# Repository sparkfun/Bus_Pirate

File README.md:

Bus Pirate
==========

*Bus Pirate [(TOL-12942)](https://www.sparkfun.com/products/12942)*

This is a troubleshooting tool that communicates between a PC and any embedded device over most standard serial protocols, which
include I<sup>2</sup>C, SPI, and asynchronous serial.

Repository Contents
-------------------

* **/Hardware** &mdash; All Eagle design files (.brd, .sch)
* **/Production** &mdash; Production panel file (.brd)
* **/Software** &mdash; Minimal Python example demonstrating binary mode

Documentation
--------------
* **[Hookup Guide](https://learn.sparkfun.com/tutorials/bus-pirate-v36a-hookup-guide)** &mdash; Basic hookup guide for the Bus Pirate.
* **[SparkFun Fritzing repo](https://github.com/sparkfun/Fritzing_Parts)** &mdash; Fritzing diagrams for SparkFun products.

Product Versions
----------------
* [TOL-12942](https://www.sparkfun.com/products/12942) &mdash; Serial protocol troubleshooting tool

Version History
---------------
* [v3.6a](https://www.sparkfun.com/products/12942) &mdash; Updated main connector wire colors/locations and improved power regulation
* [v36](https://www.sparkfun.com/products/retired/9544) &mdash; Original version produced by SparkFun

License Information
-------------------

This product is _**open source**_!

Please review the LICENSE.md file for license information.

If you have any questions or concerns on licensing, please contact techsupport@sparkfun.com.

Distributed as-is; no warranty is given.

- Your friends at SparkFun.

This is a collaboration with Ian Lesnet.

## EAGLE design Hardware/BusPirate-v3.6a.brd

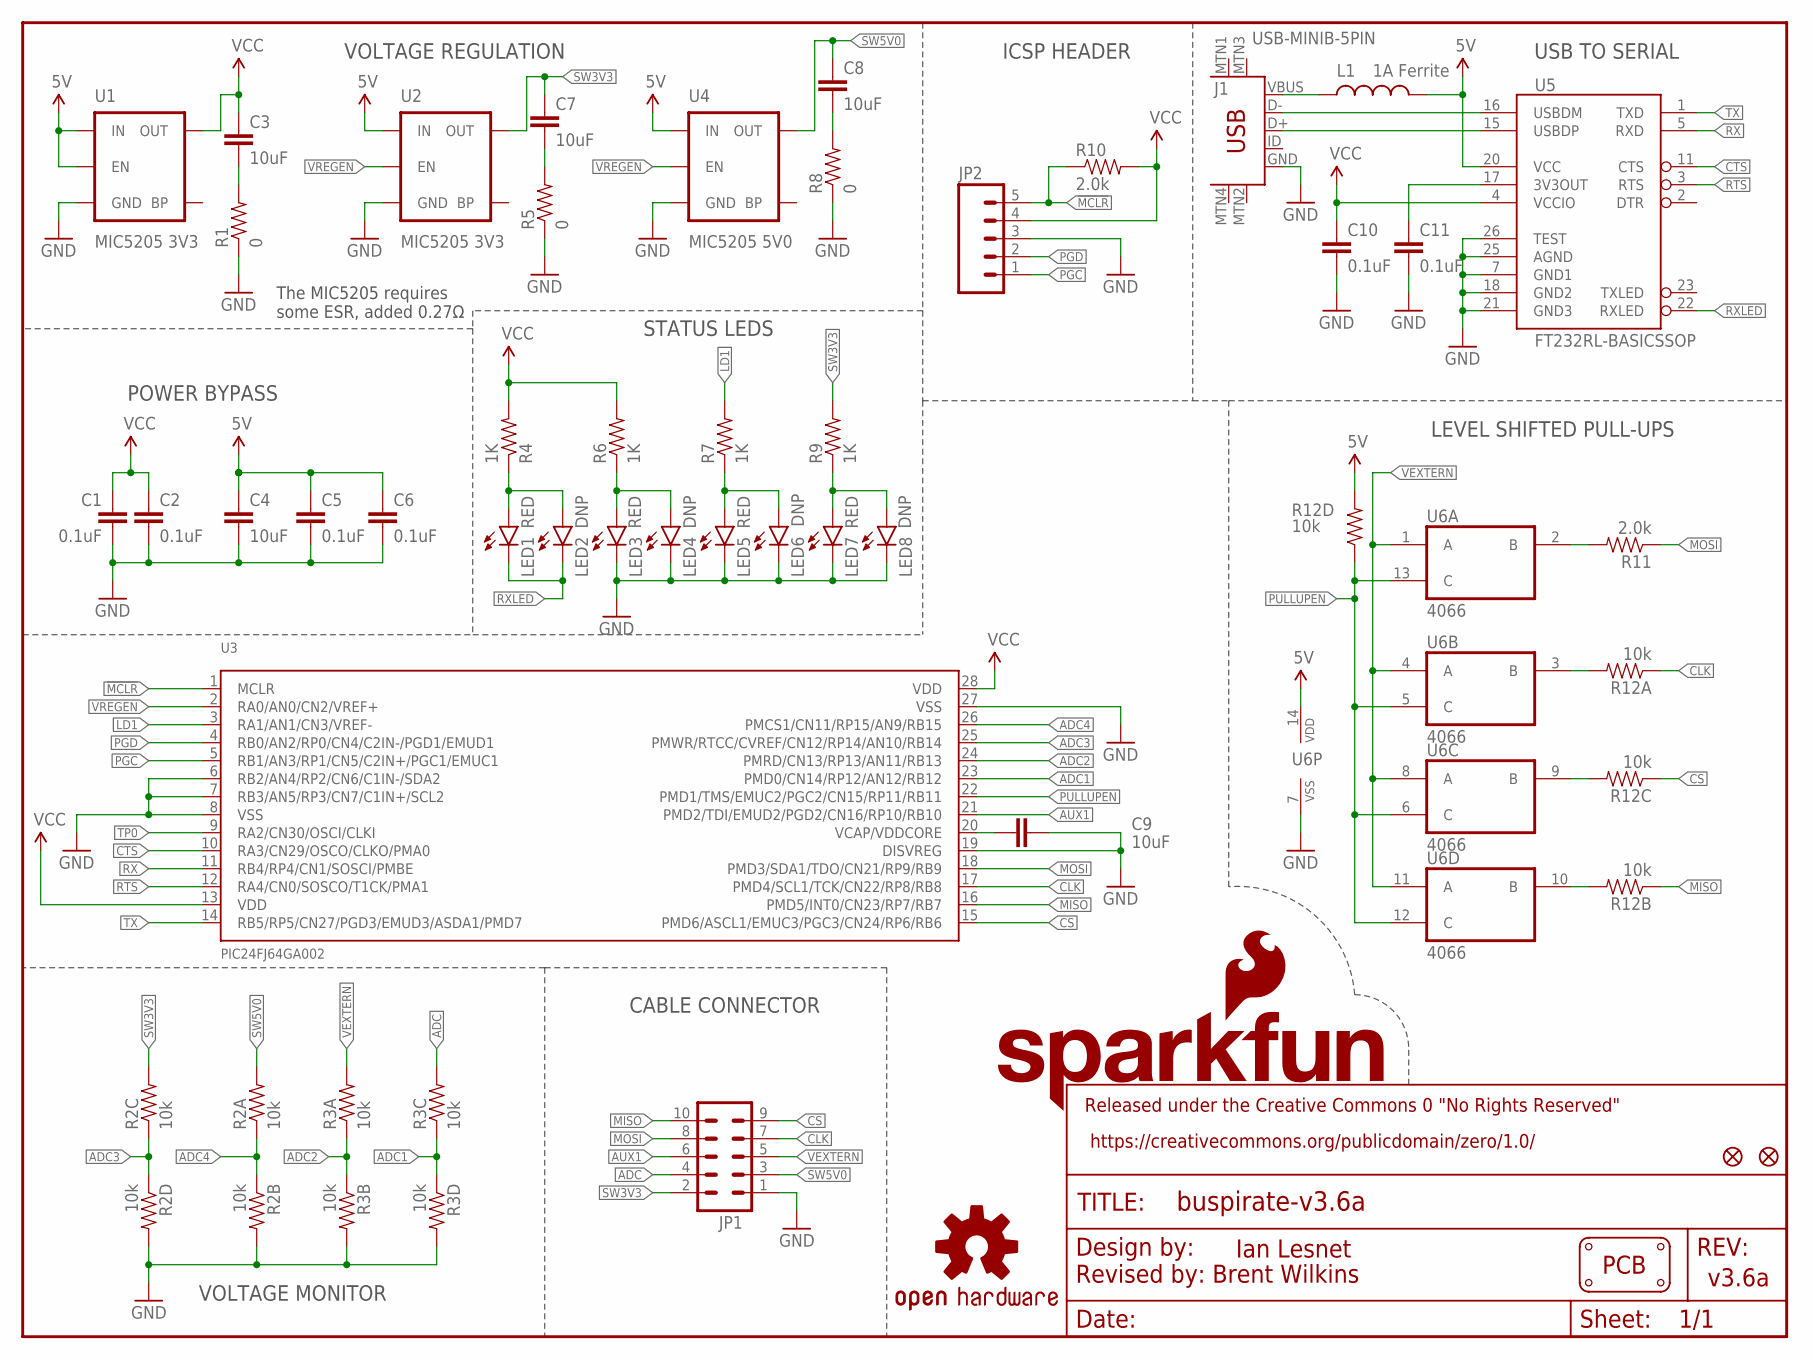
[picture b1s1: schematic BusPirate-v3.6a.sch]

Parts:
C1, C2, C5, C6, C10, C11: 0.1uF; 0603-CAP
C3, C4, C7, C8, C9: 10uF; 0805-CAP
FID1, FID2: FIDUCIAL1X2; FIDUCIAL-1X2
J1: USB-MINIB-5PIN; USB-MINIB
JP1: M05X2SHD_SMD; 2X5-SHROUDED_SMD
JP2: M05PTH; 1X05
L1: 1A Ferrite; 0603
LED1, LED3, LED5, LED7: RED; LED-0603
LED2, LED4, LED6, LED8: DNP; LED-0603
LOGO1: OSHW-LOGOL; OSHW-LOGO-L
LOGO2: SFE_LOGO_NAME_FLAME.1_INCH; SFE_LOGO_NAME_FLAME_.1
PCB1: PCB_DP_RECTANGLE-37X60; DP6037_V1
R1, R5, R8: 0; 0603
R2, R3, R12: 10k; 4XARRAY
R4, R6, R7, R9: 1K; 0603-RES
R10, R11: 2.0k; 0603-RES
U1, U2: MIC5205 3V3; SOT23-5
U3: PIC24FJ64GA002; SSOP28
U4: MIC5205 5V0; SOT23-5
U5: FT232RL-BASICSSOP; SSOP28DB
U6: 4066; TSSOP14

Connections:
5V: C4.1, C5.1, C6.1, L1.2, R12.5 (2), U1.1 (IN), U1.3 (EN), U2.1 (IN), U4.1 (IN), U5.20 (VCC), U6.14 (VDD)
!MCLR: JP2.5, R10.1, U3.1 (MCLR)
$N26: J1.VBUS, L1.1
ADC: JP1.4, R3.6 (2)
ADC1: R3.3 (1), R3.4 (1), U3.23 (PMD0/CN14/RP12/AN12/RB12)
ADC2: R3.1, R3.2 (1), U3.24 (PMRD/CN13/RP13/AN11/RB13)
ADC3: R2.3 (1), R2.4 (1), U3.25 (PMWR/RTCC/CVREF/CN12/RP14/AN10/RB14)
ADC4: R2.1, R2.2 (1), U3.26 (PMCS1/CN11/RP15/AN9/RB15)
AUX1: JP1.6, U3.21 (PMD2/TDI/EMUD2/PGD2/CN16/RP10/RB10)
CLK: JP1.7, R12.1, U3.17 (PMD4/SCL1/TCK/CN22/RP8/RB8)
CS: JP1.9, R12.3 (1), U3.15 (PMD6/ASCL1/EMUC3/PGC3/CN24/RP6/RB6)
CTS: U3.10 (RA3/CN29/OSCO/CLKO/PMA0), U5.11 (CTS)
D+: J1.D+, U5.15 (USBDP)
D-: J1.D-, U5.16 (USBDM)
GND: C1.2, C2.2, C4.2, C5.2, C6.2, C9.2, C10.2, C11.2, J1.GND, JP1.1, JP2.3, LED3.C, LED4.C, LED5.C, LED6.C, LED7.C, LED8.C, R1.1, R2.5 (2), R2.7 (2), R3.5 (2), R3.7 (2), R5.1, R8.1, U1.2 (GND), U2.2 (GND), U3.6 (RB2/AN4/RP2/CN6/C1IN-/SDA2), U3.7 (RB3/AN5/RP3/CN7/C1IN+/SCL2), U3.8 (VSS), U3.19 (DISVREG), U3.27 (VSS), U4.2 (GND), U5.7 (GND1), U5.18 (GND2), U5.21 (GND3), U5.25 (AGND), U5.26 (TEST), U6.7 (VSS)
LD1: R7.2, U3.3 (RA1/AN1/CN3/VREF-)
MISO: JP1.10, R12.2 (1), U3.16 (PMD5/INT0/CN23/RP7/RB7)
MOSI: JP1.8, R11.1, U3.18 (PMD3/SDA1/TDO/CN21/RP9/RB9)
unnamed: R11.2, U6.2 (B)
unnamed: R12.6 (2), U6.9 (B)
unnamed: C9.1, U3.20 (VCAP/VDDCORE)
unnamed: R12.7 (2), U6.10 (B)
unnamed: R12.8 (2), U6.3 (B)
unnamed: LED5.A, LED6.A, R7.1
unnamed: LED3.A, LED4.A, R6.1
unnamed: C3.2, R1.2
unnamed: C11.1, U5.17 (3V3OUT)
unnamed: C7.2, R5.2
unnamed: C8.2, R8.2
unnamed: LED1.A, LED2.A, R4.1
unnamed: LED7.A, LED8.A, R9.1
PGC: JP2.1, U3.5 (RB1/AN3/RP1/CN5/C2IN+/PGC1/EMUC1)
PGD: JP2.2, U3.4 (RB0/AN2/RP0/CN4/C2IN-/PGD1/EMUD1)
PULLUPEN: R12.4 (1), U3.22 (PMD1/TMS/EMUC2/PGC2/CN15/RP11/RB11), U6.5 (C), U6.6 (C), U6.12 (C), U6.13 (C)
RTS: U3.12 (RA4/CN0/SOSCO/T1CK/PMA1), U5.3 (RTS)
RX: U3.11 (RB4/RP4/CN1/SOSCI/PMBE), U5.5 (RXD)
RXLED: LED1.C, LED2.C, U5.22 (RXLED)
SW3V3: C7.1, JP1.2, R2.6 (2), R9.2, U2.5 (OUT)
SW5V0: C8.1, JP1.3, R2.8 (2), U4.5 (OUT)
TP0: U3.9 (RA2/CN30/OSCI/CLKI)
TX: U3.14 (RB5/RP5/CN27/PGD3/EMUD3/ASDA1/PMD7), U5.1 (TXD)
VCC: C1.1, C2.1, C3.1, C10.1, JP2.4, R4.2, R6.2, R10.2, U1.5 (OUT), U3.13 (VDD), U3.28 (VDD), U5.4 (VCCIO)
VEXTERN: JP1.5, R3.8 (2), U6.1 (A), U6.4 (A), U6.8 (A), U6.11 (A)
VREGEN: U2.3 (EN), U3.2 (RA0/AN0/CN2/VREF+), U4.3 (EN)

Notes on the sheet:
Revised by: Brent Wilkins
Ian Lesnet
v3.6a
VOLTAGE REGULATION
VOLTAGE MONITOR
USB TO SERIAL
STATUS LEDS
POWER BYPASS
ICSP HEADER
LEVEL SHIFTED PULL-UPS
CABLE CONNECTOR
The MIC5205 requires some ESR, added 0.27Ω
Date:
Sheet:
REV:
TITLE:
Released under the Creative Commons 0 "No Rights Reserved"
https://creativecommons.org/publicdomain/zero/1.0/
Design by:

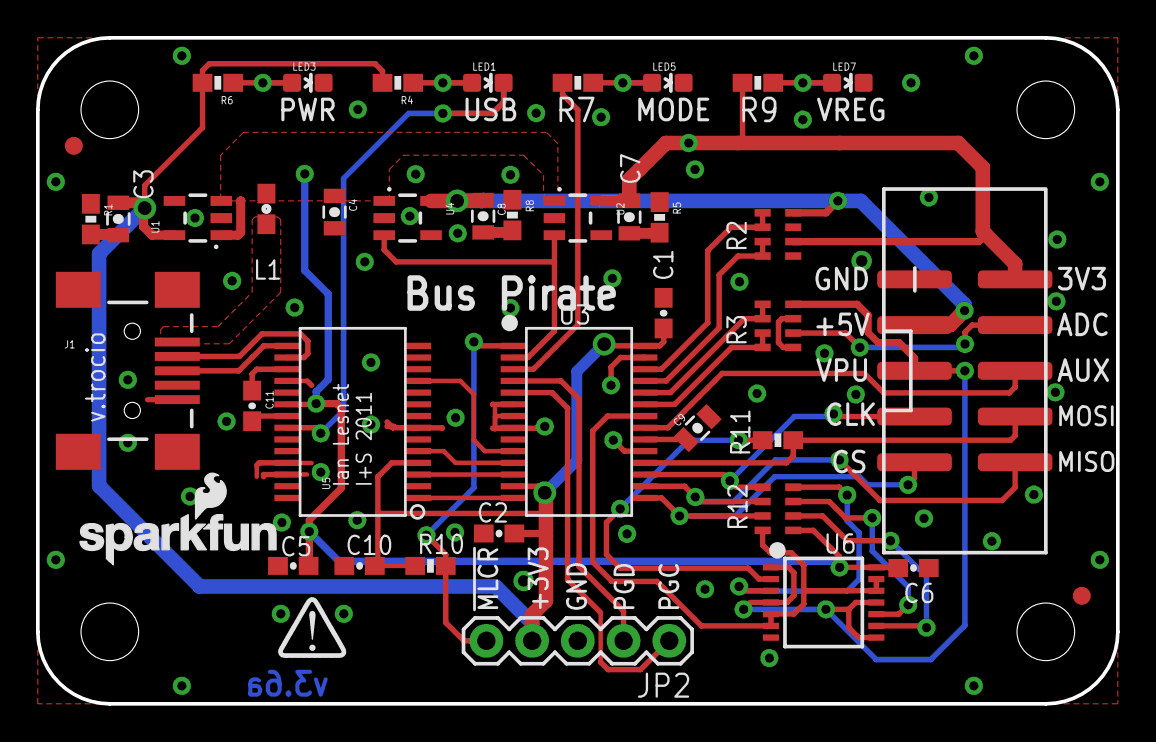
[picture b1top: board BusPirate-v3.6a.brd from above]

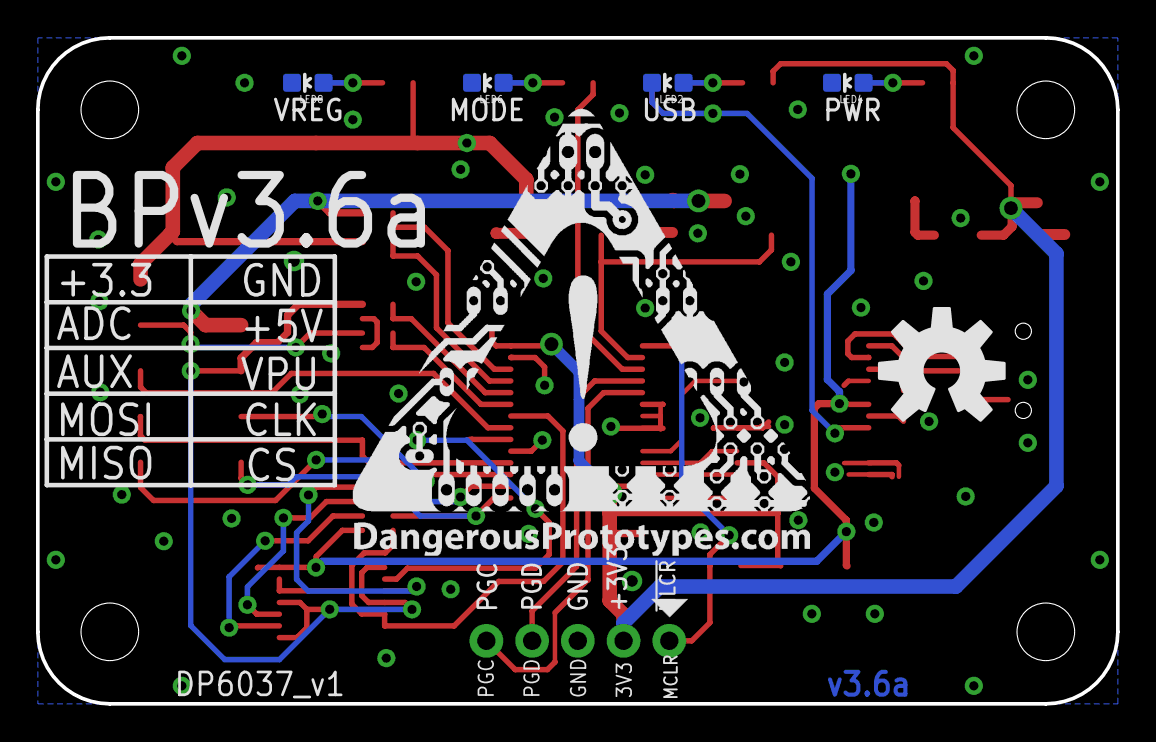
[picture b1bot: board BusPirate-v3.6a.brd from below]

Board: 2 copper layers, 60.0 x 37.0 mm, 48 parts (6 on the bottom side), 43 nets.

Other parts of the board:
U$1: DP-LOGO
U$3: DP_LOGO_ART_1X1

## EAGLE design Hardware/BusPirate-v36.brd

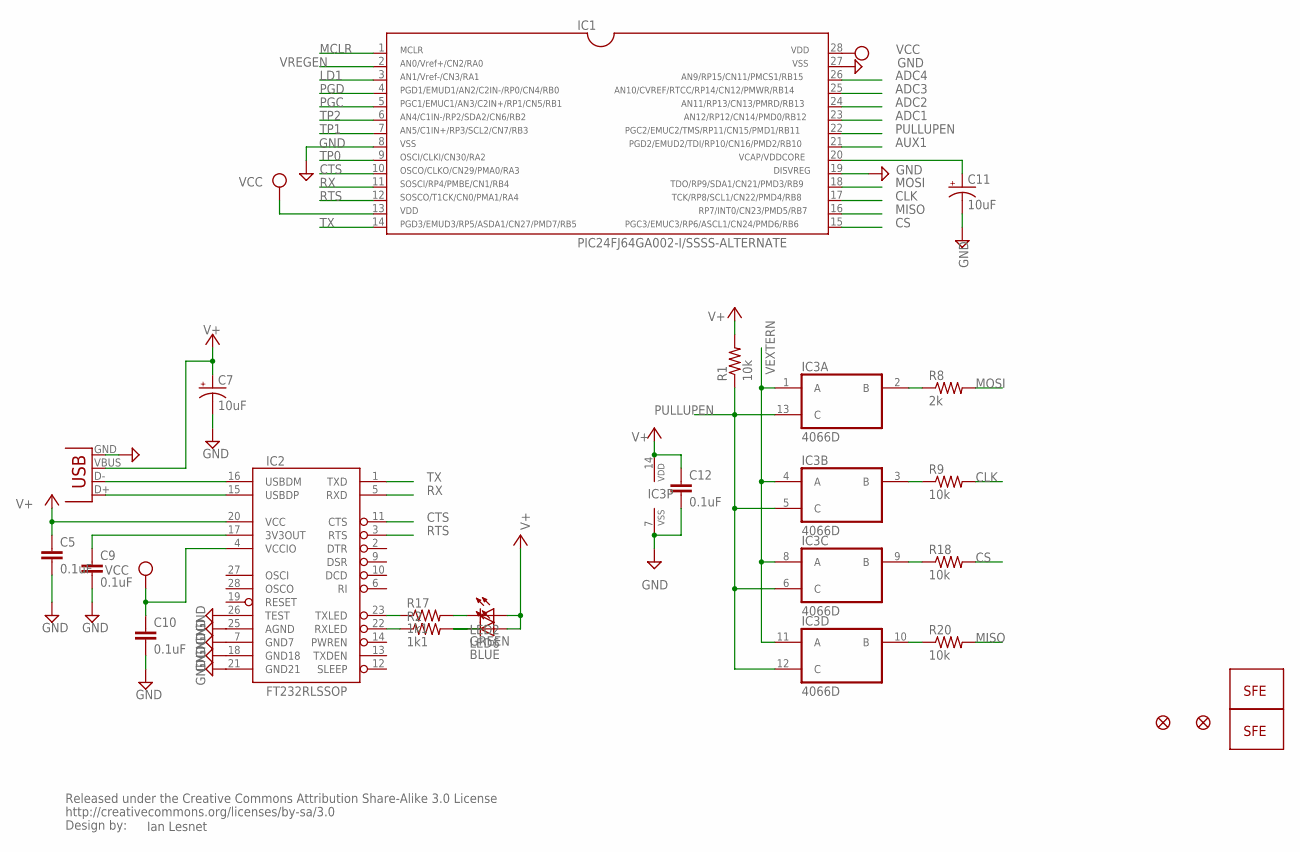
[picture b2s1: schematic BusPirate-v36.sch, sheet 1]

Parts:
C5, C9, C10, C12: 0.1uF; 0402-CAP
C7, C11: 10uF; EIA3216
IC1: PIC24FJ64GA002-I/SSSS-ALTERNATE; SSOP28DB
IC2: FT232RLSSOP; SSOP28DB
IC3: 4066D; SO14
J1: USBSMD; USB-MINIB
JP1, JP2: LOGO-SFENEW; SFE-NEW-WEBLOGO
JP3, JP4: FIDUCIAL1X2; FIDUCIAL-1X2
LED2: GREEN; LED-0603
LED6: BLUE; LED-0603
R1, R9, R18, R20: 10k; 0402-RES
R2, R17: 1k1; 0402-RES
R8: 2k; 0402-RES
U$2: CREATIVE_COMMONS

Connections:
ADC1: IC1.23; also elsewhere on the board
ADC2: IC1.24; also elsewhere on the board
ADC3: IC1.25; also elsewhere on the board
ADC4: IC1.26; also elsewhere on the board
AUX1: IC1.21; also elsewhere on the board
CLK: IC1.17, R9.2; also elsewhere on the board
CS: IC1.15, R18.2; also elsewhere on the board
CTS: IC1.10, IC2.11 (CTS)
GND: C5.2, C7.C (-), C9.2, C10.2, C11.C (-), C12.2, IC1.8, IC1.19, IC1.27, IC2.7 (GND7), IC2.18 (GND18), IC2.21 (GND21), IC2.25 (AGND), IC2.26 (TEST), IC3.7 (VSS), J1.GND; also elsewhere on the board
LD1: IC1.3; also elsewhere on the board
MCLR: IC1.1; also elsewhere on the board
MISO: IC1.16, R20.2; also elsewhere on the board
MOSI: IC1.18, R8.2; also elsewhere on the board
unnamed: IC3.2 (B), R8.1
unnamed: IC3.3 (B), R9.1
unnamed: C11.A (+), IC1.20
unnamed: IC3.10 (B), R20.1
unnamed: IC3.9 (B), R18.1
unnamed: IC2.23 (TXLED), R17.1
unnamed: C9.1, IC2.17 (3V3OUT)
unnamed: LED2.C, R17.2
unnamed: IC2.22 (RXLED), R2.1
unnamed: LED6.C, R2.2
unnamed: IC2.15 (USBDP), J1.D+
unnamed: IC2.16 (USBDM), J1.D-
PGC: IC1.5; also elsewhere on the board
PGD: IC1.4; also elsewhere on the board
PULLUPEN: IC1.22, IC3.5 (C), IC3.6 (C), IC3.12 (C), IC3.13 (C), R1.1
RTS: IC1.12, IC2.3 (RTS)
RX: IC1.11, IC2.5 (RXD)
TP0: IC1.9
TP1: IC1.7
TP2: IC1.6
TX: IC1.14, IC2.1 (TXD)
V+: C5.1, C7.A (+), C12.1, IC2.20 (VCC), IC3.14 (VDD), J1.VBUS, LED2.A, LED6.A, R1.2; also elsewhere on the board
VCC: C10.1, IC1.13, IC1.28, IC2.4 (VCCIO); also elsewhere on the board
VEXTERN: IC3.1 (A), IC3.4 (A), IC3.8 (A), IC3.11 (A); also elsewhere on the board
VREGEN: IC1.2; also elsewhere on the board

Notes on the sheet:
Ian Lesnet

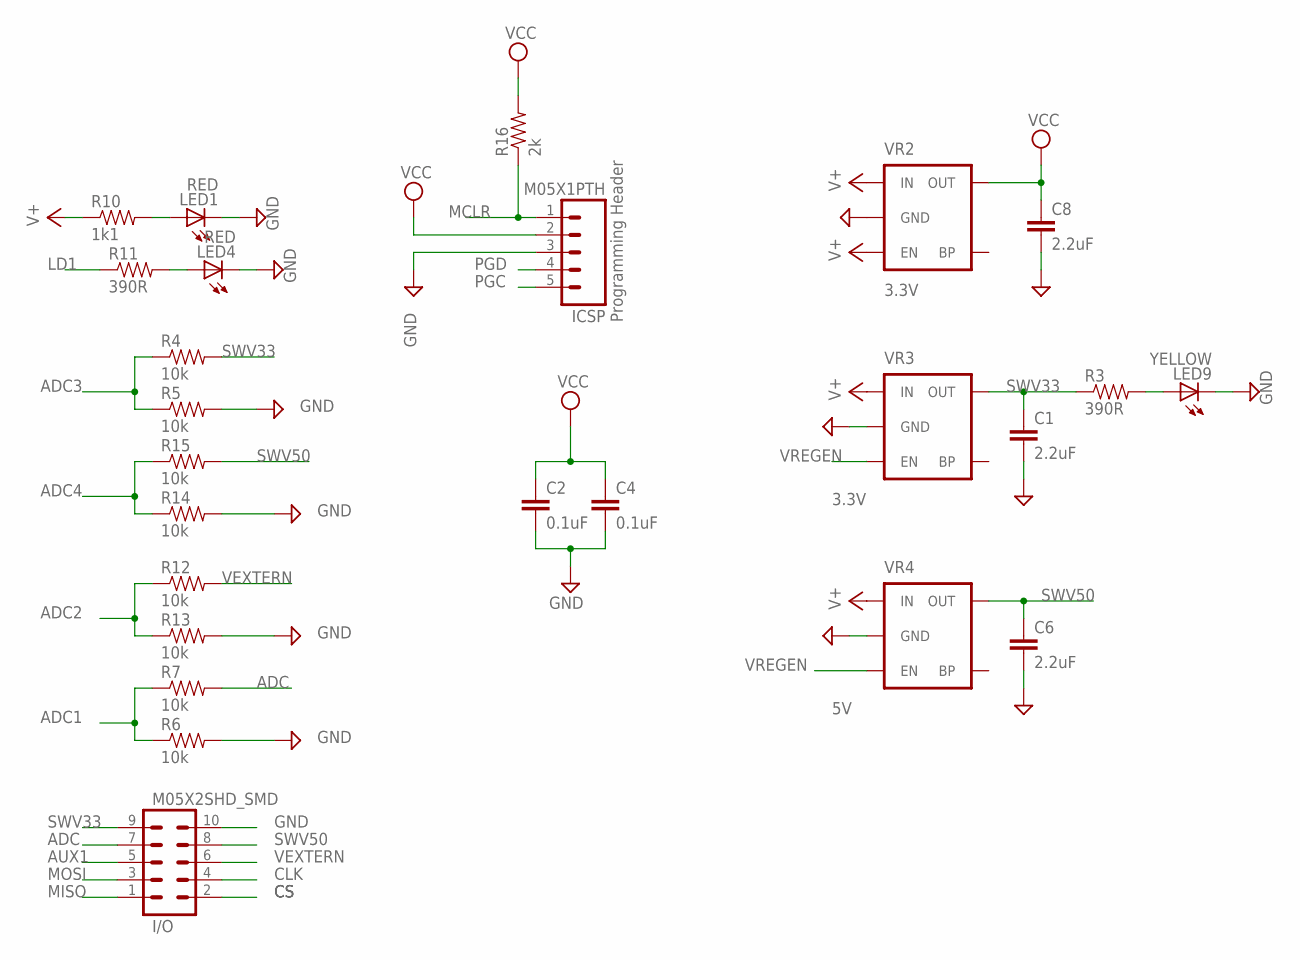
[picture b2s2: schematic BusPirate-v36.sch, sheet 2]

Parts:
C1, C6, C8: 2.2uF; 0402-CAP
C2, C4: 0.1uF; 0402-CAP
I/O: M05X2SHD_SMD; 2X5-SHROUDED_SMD
ICSP: M05X1PTH; 1X05
LED1, LED4: RED; LED-0603
LED9: YELLOW; LED-0603
R3, R11: 390R; 0402-RES
R4, R5, R6, R7, R12, R13, R14, R15: 10k; 0402-RES
R10: 1k1; 0402-RES
R16: 2k; 0402-RES
VR2, VR3: 3.3V; SOT23-5
VR4: 5V; SOT23-5

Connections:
ADC: I/O.7, R7.2
ADC1: R6.1, R7.1; also elsewhere on the board
ADC2: R12.1, R13.1; also elsewhere on the board
ADC3: R4.1, R5.1; also elsewhere on the board
ADC4: R14.1, R15.1; also elsewhere on the board
AUX1: I/O.5; also elsewhere on the board
CLK: I/O.4; also elsewhere on the board
CS: I/O.2; also elsewhere on the board
GND: C1.2, C2.2, C4.2, C6.2, C8.2, I/O.10, ICSP.3, LED1.C, LED4.C, LED9.C, R5.2, R6.2, R13.2, R14.2, VR2.2 (GND), VR3.2 (GND), VR4.2 (GND); also elsewhere on the board
LD1: R11.1; also elsewhere on the board
MCLR: ICSP.1, R16.1; also elsewhere on the board
MISO: I/O.1; also elsewhere on the board
MOSI: I/O.3; also elsewhere on the board
unnamed: LED4.A, R11.2
unnamed: LED1.A, R10.2
unnamed: LED9.A, R3.2
PGC: ICSP.5; also elsewhere on the board
PGD: ICSP.4; also elsewhere on the board
SWV33: C1.1, I/O.9, R3.1, R4.2, VR3.5 (OUT)
SWV50: C6.1, I/O.8, R15.2, VR4.5 (OUT)
V+: R10.1, VR2.1 (IN), VR2.3 (EN), VR3.1 (IN), VR4.1 (IN); also elsewhere on the board
VCC: C2.1, C4.1, C8.1, ICSP.2, R16.2, VR2.5 (OUT); also elsewhere on the board
VEXTERN: I/O.6, R12.2; also elsewhere on the board
VREGEN: VR3.3 (EN), VR4.3 (EN); also elsewhere on the board

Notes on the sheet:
Programming Header

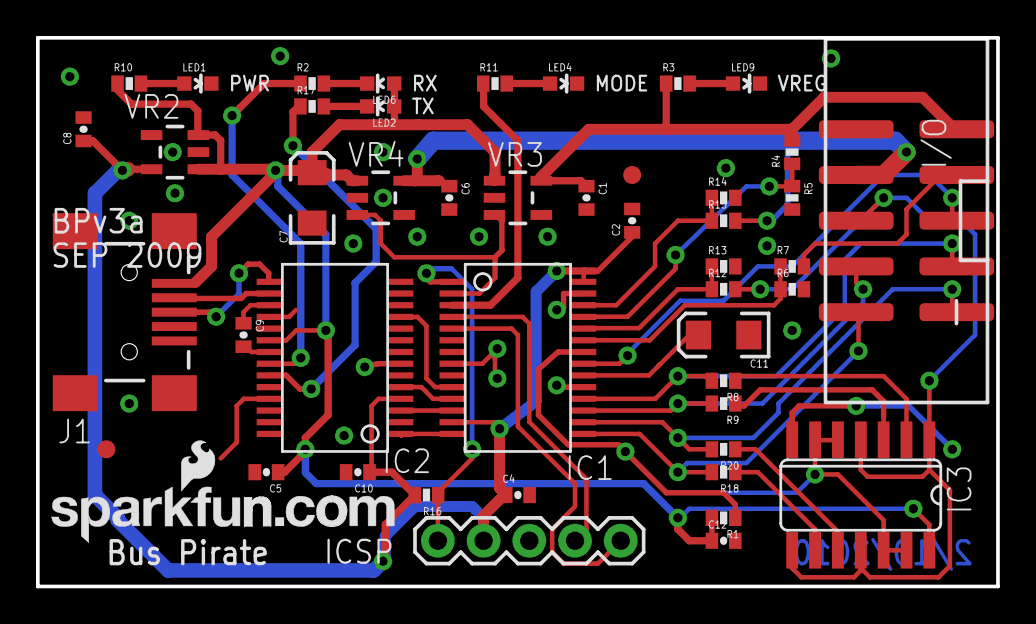
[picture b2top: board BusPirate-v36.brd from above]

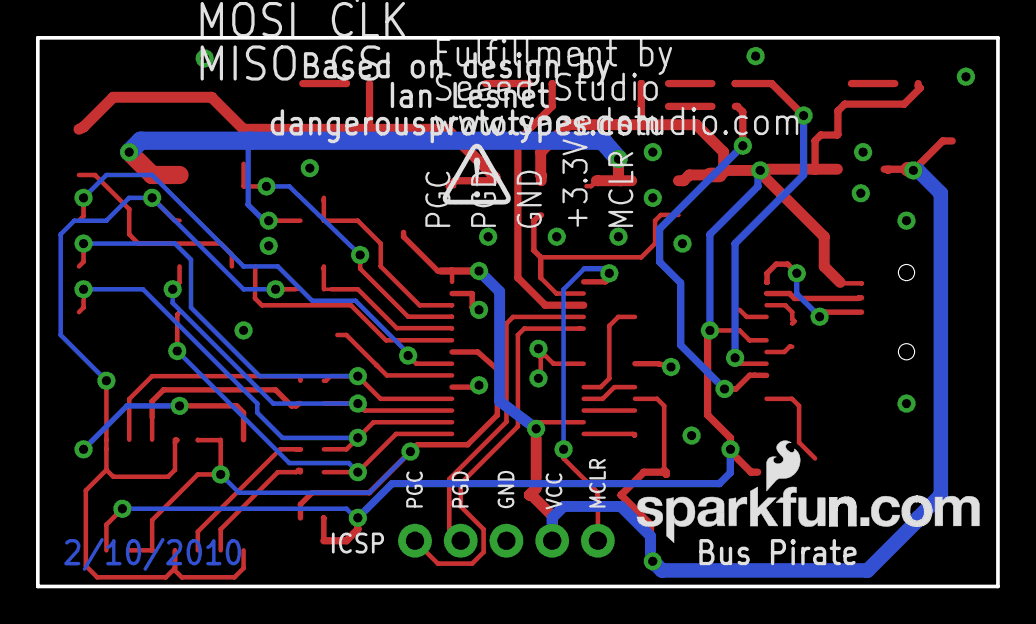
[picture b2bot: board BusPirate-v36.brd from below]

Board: 2 copper layers, 53.3 x 30.5 mm, 50 parts (2 on the bottom side), 41 nets.

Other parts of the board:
U$1: DP-LOGO

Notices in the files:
parts and their libraries:
SparkFun-Aesthetics: Licensing: Creative Commons ShareAlike 4.0 International - https://creativecommons.org/licenses/by-sa/4.0
SparkFun: Released under the Creative Commons Attribution Share-Alike 3.0 License
SparkFun: http://creativecommons.org/licenses/by-sa/3.0
